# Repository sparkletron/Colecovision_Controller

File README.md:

# Colecovision Controller
Controller for colecovision  

author: Jay Convertino  

date: 2022.01.31  

license: MIT (All files in repo)

## Release Versions
### Current
  - release_v1.0.1 : Switched ARM/FIRE buttons to match original controller

### Past
  - release_v1
  
## Requirements
  - KiCad v7

## Building
  - KiCad can generate any gerbers you are looking for.
  - Board built and tested using a T-Tech 5000 CNC mill v4 isopro.

## Parts list
|  REF  |      PART NUMBER      | QUANTITY |
|:---   |:---                   |:---      |
|D1-D28 |1N914                  |28        |
|S1-S18 |Omron B3F-10XX         |18        |
|J1     |RB-GEN-5839(cable)     |1         |
|H1-H8  |#4 x 5/8" Pan,Sheet    |8         |
|NA     |SHELL TOP (3D print)   |1         |
|NA     |SHELL BOT (3D print)   |1         |
|NA     |NUMPAD (3D print)      |12        |
|NA     |DPAD (3D print)        |1         |
|NA     |FIRE BUTTON (3D print) |2         |

## Assembly Tips
  - 3D print using ABS plastic.
    - 100.5% for shell size
    - 100% size for all buttons
  - Single sided PCB
  - Only the smallest diode footprint need to be installed vertically.
  - 8 Screws 
    - 5/8th inch long at most.
    - #4 screw 0.112 inch diameter.
    - Course thread (sheet metal type).
    - Pan Head no larger then 3/16th of an inch.

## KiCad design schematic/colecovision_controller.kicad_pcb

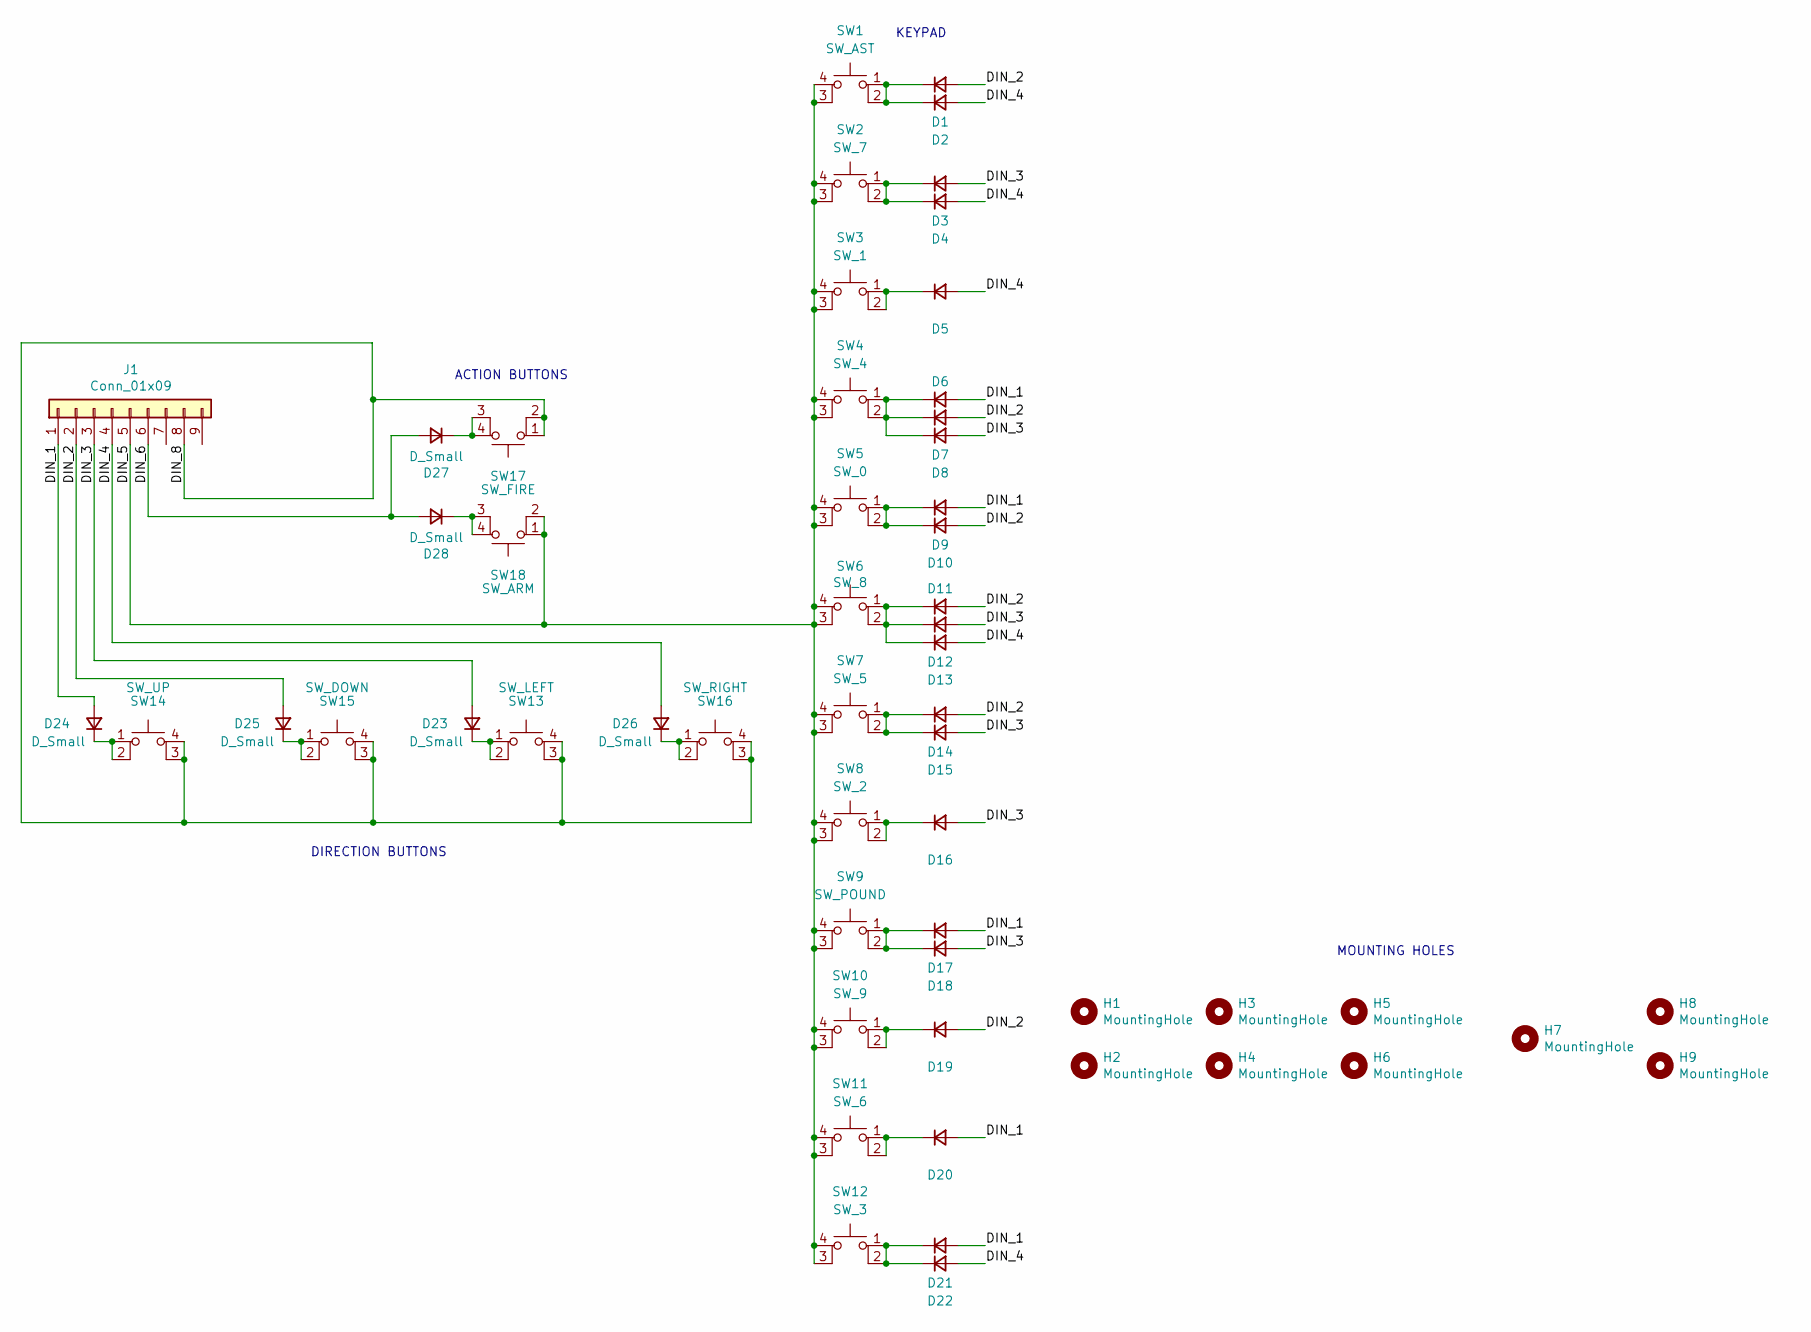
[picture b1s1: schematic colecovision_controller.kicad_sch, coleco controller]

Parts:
D1, D7, D10, D11, D14, D19, D23, D24, D25, D26, D27, D28: D_Small; D_DO-35_SOD27_P7.62mm_Horizontal
D2, D4, D5, D13, D22: D_Small; D_DO-35_SOD27_P2.54mm_Vertical_KathodeUp
D3, D8, D12, D15, D16, D18: D_Small; D_DO-35_SOD27_P5.08mm_Vertical_KathodeUp
D6, D9, D17, D20, D21: D_Small; D_DO-35_SOD27_P10.16mm_Horizontal
H1, H2, H3, H4, H5, H6, H8, H9: MountingHole; MountingHole_4.3mm_M4
H7: MountingHole; MountingHole_2.7mm_M2.5
J1: Conn_01x09; PinSocket_1x09_P2.54mm_Vertical
SW1: SW_AST; SW_TH_Tactile_Omron_B3F-10xx
SW2: SW_7; SW_TH_Tactile_Omron_B3F-10xx
SW3: SW_1; SW_TH_Tactile_Omron_B3F-10xx
SW4: SW_4; SW_TH_Tactile_Omron_B3F-10xx
SW5: SW_0; SW_TH_Tactile_Omron_B3F-10xx
SW6: SW_8; SW_TH_Tactile_Omron_B3F-10xx
SW7: SW_5; SW_TH_Tactile_Omron_B3F-10xx
SW8: SW_2; SW_TH_Tactile_Omron_B3F-10xx
SW9: SW_POUND; SW_TH_Tactile_Omron_B3F-10xx
SW10: SW_9; SW_TH_Tactile_Omron_B3F-10xx
SW11: SW_6; SW_TH_Tactile_Omron_B3F-10xx
SW12: SW_3; SW_TH_Tactile_Omron_B3F-10xx
SW13: SW_LEFT; SW_TH_Tactile_Omron_B3F-10xx
SW14: SW_UP; SW_TH_Tactile_Omron_B3F-10xx
SW15: SW_DOWN; SW_TH_Tactile_Omron_B3F-10xx
SW16: SW_RIGHT; SW_TH_Tactile_Omron_B3F-10xx
SW17: SW_FIRE; SW_TH_Tactile_Omron_B3F-10xx
SW18: SW_ARM; SW_TH_Tactile_Omron_B3F-10xx

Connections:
/DIN_1: D6.2 (A), D9.2 (A), D17.2 (A), D20.2 (A), D21.2 (A), D24.2 (A), J1.1
/DIN_2: D1.2 (A), D7.2 (A), D10.2 (A), D11.2 (A), D14.2 (A), D19.2 (A), D25.2 (A), J1.2
/DIN_3: D3.2 (A), D8.2 (A), D12.2 (A), D15.2 (A), D16.2 (A), D18.2 (A), D23.2 (A), J1.3
/DIN_4: D2.2 (A), D4.2 (A), D5.2 (A), D13.2 (A), D22.2 (A), D26.2 (A), J1.4
/DIN_5: J1.5, SW1.3 (K), SW1.4 (A), SW2.3 (K), SW2.4 (A), SW3.3 (K), SW3.4 (A), SW4.3 (K), SW4.4 (A), SW5.3 (K), SW5.4 (A), SW6.3 (K), SW6.4 (A), SW7.3 (K), SW7.4 (A), SW8.3 (K), SW8.4 (A), SW9.3 (K), SW9.4 (A), SW10.3 (K), SW10.4 (A), SW11.3 (K), SW11.4 (A), SW12.3 (K), SW12.4 (A), SW18.1, SW18.2
/DIN_6: D27.2 (A), D28.2 (A), J1.6
/DIN_8: J1.8, SW13.3 (K), SW13.4 (A), SW14.3 (K), SW14.4 (A), SW15.3 (K), SW15.4 (A), SW16.3 (K), SW16.4 (A), SW17.1, SW17.2
unnamed: D1.1 (K), D2.1 (K), SW1.1, SW1.2
unnamed: D3.1 (K), D4.1 (K), SW2.1, SW2.2
unnamed: D5.1 (K), SW3.1, SW3.2
unnamed: D6.1 (K), D7.1 (K), D8.1 (K), SW4.1, SW4.2
unnamed: D9.1 (K), D10.1 (K), SW5.1, SW5.2
unnamed: D11.1 (K), D12.1 (K), D13.1 (K), SW6.1, SW6.2
unnamed: D14.1 (K), D15.1 (K), SW7.1, SW7.2
unnamed: D16.1 (K), SW8.1, SW8.2
unnamed: D17.1 (K), D18.1 (K), SW9.1, SW9.2
unnamed: D19.1 (K), SW10.1, SW10.2
unnamed: D20.1 (K), SW11.1, SW11.2
unnamed: D21.1 (K), D22.1 (K), SW12.1, SW12.2
unnamed: D23.1 (K), SW13.1, SW13.2
unnamed: D24.1 (K), SW14.1, SW14.2
unnamed: D25.1 (K), SW15.1, SW15.2
unnamed: D26.1 (K), SW16.1, SW16.2
unnamed: D27.1 (K), SW17.3 (K), SW17.4 (A)
unnamed: D28.1 (K), SW18.3 (K), SW18.4 (A)

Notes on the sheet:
KEYPAD
DIRECTION BUTTONS
MOUNTING HOLES
ACTION BUTTONS

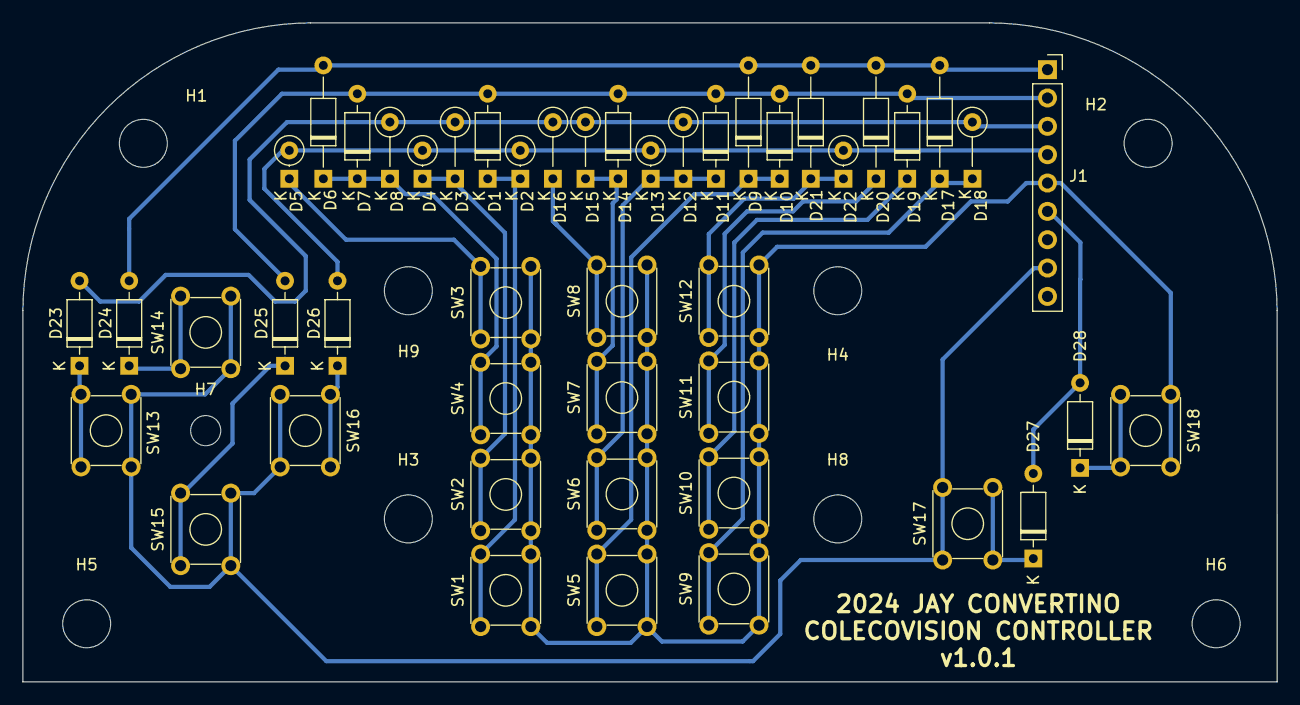
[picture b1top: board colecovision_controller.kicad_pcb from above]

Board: 2 copper layers, 112.4 x 59.1 mm, 56 parts (0 on the bottom side), 25 nets.

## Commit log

2022-01-31 inital commit
2022-02-13 updated readme with build info
2022-02-13 messed up diode number
2022-02-13 fixed naming, model names match part number
2022-02-13 added proper screw sizes
2022-02-13 fixed grammer
2023-01-16 update to kicad 6, mit license added
2024-02-07 fixed edge cuts for all builders, added seperate layer for mill call edge cute mill
2024-02-07 cut* and added ignore rule for kicad backups
2024-03-25 fixed for github
2024-09-19 updated to fix arm/fire button position. Now matches original controller.
2024-09-19 cleanup drc
2025-01-29 add updated models for control design. Deeper screws and better dpad
2025-04-06 thin out the base for the 3D printed parts for better fitment
2025-08-01 add pdf version of schematic
